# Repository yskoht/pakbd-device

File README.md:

# pakbd

## rev1

## rev2

## rev3

## License

This software is released under the MIT License, see LICENSE.

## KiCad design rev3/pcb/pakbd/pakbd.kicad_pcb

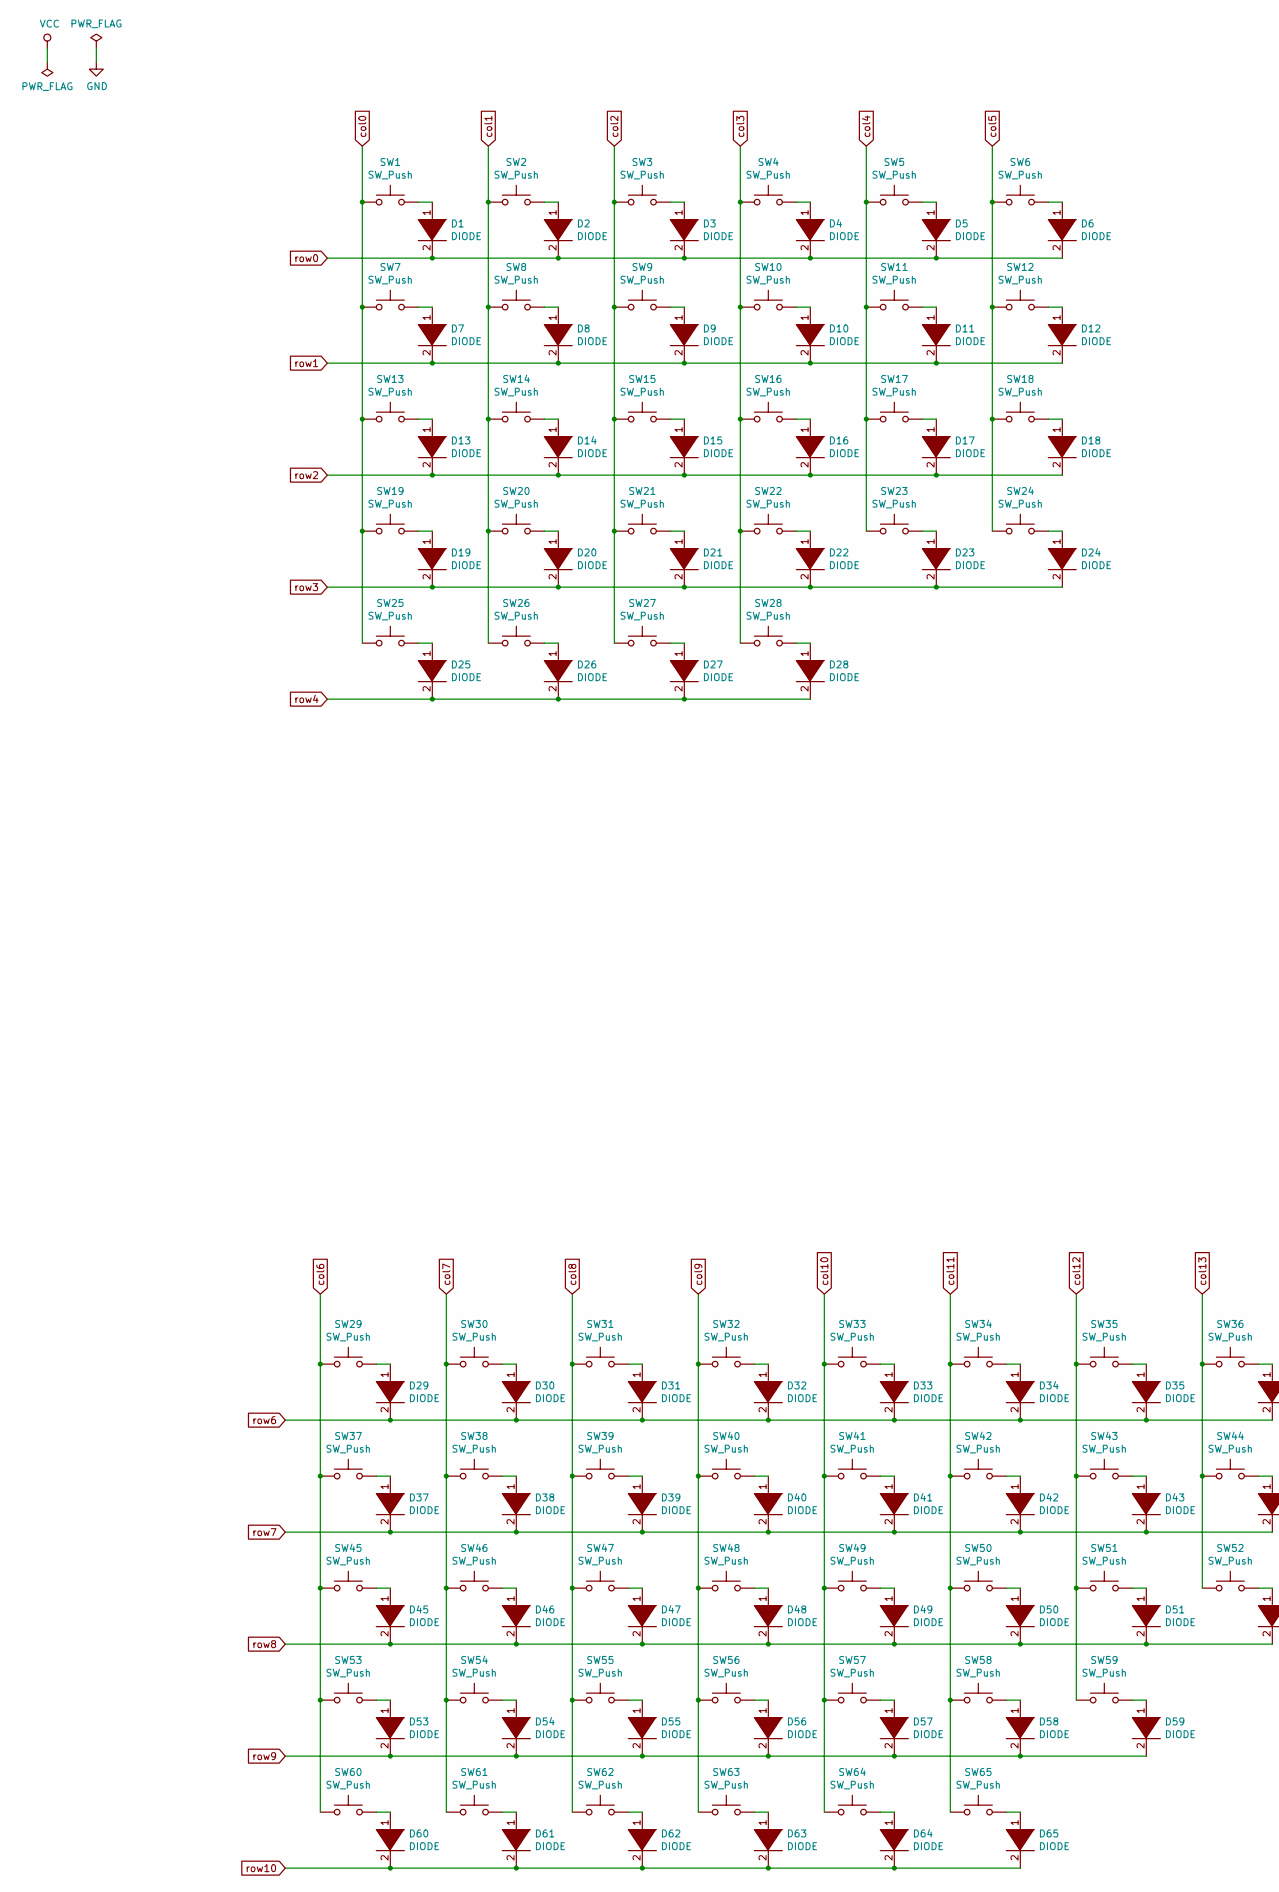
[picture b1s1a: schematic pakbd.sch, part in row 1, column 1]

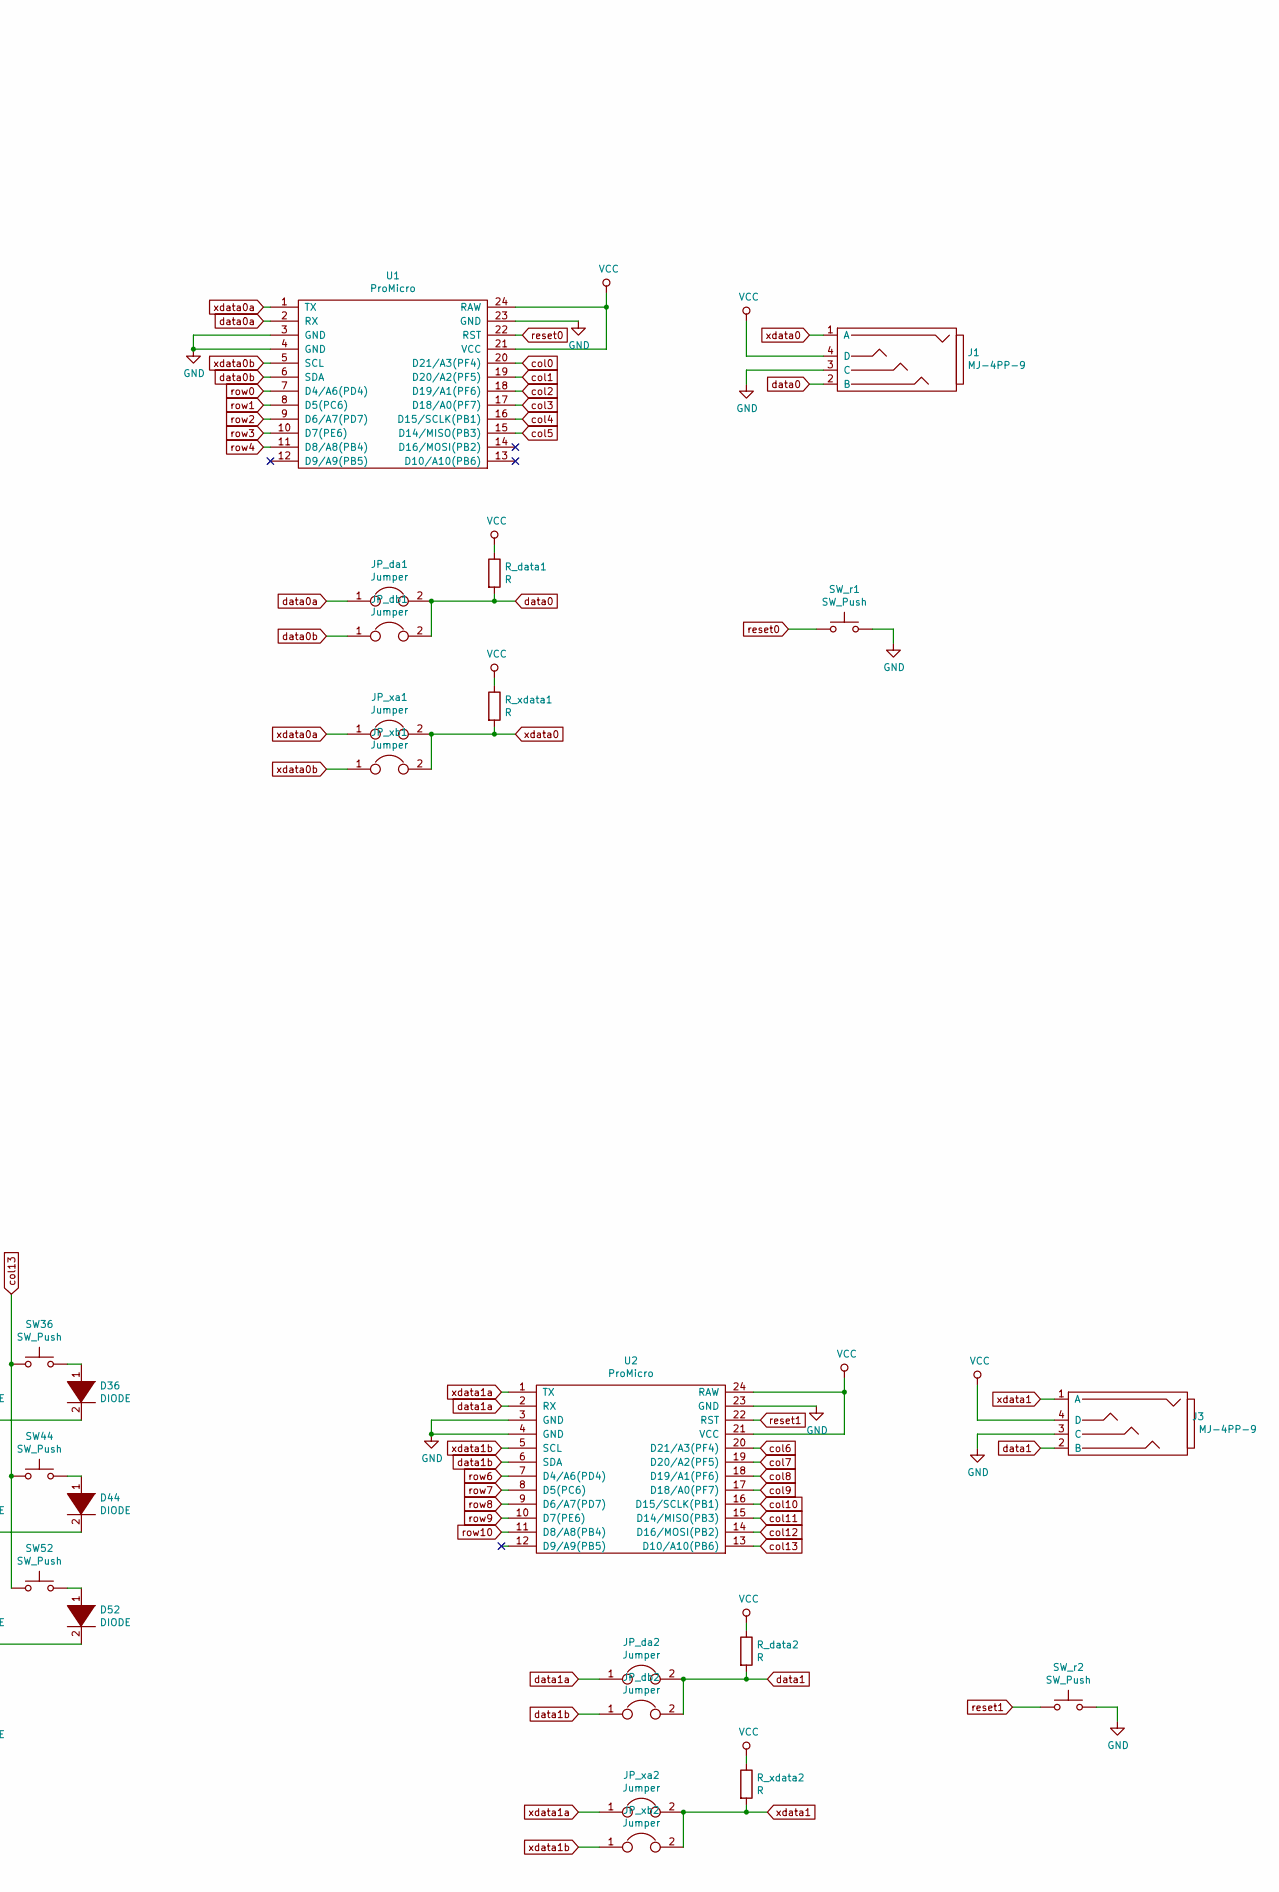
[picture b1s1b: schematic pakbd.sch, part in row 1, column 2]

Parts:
D1, D2, D3, D4, D5, D6, D7, D8, D9, D10, D11, D12, D13, D14, D15, D16, D17, D18, D19, D20, D21, D22, D23, D24, D25, D26, D27, D28, D29, D30, D31, D32, D33, D34, D35, D36, D37, D38, D39, D40, D41, D42, D43, D44, D45, D46, D47, D48, D49, D50, D51, D52, D53, D54, D55, D56, D57, D58, D59, D60, D61, D62, D63, D64, D65: DIODE; D_1206_3216Metric_Pad1.42x1.75mm_HandSolder
J1, J3: MJ-4PP-9
JP_da1, JP_da2: Jumper; SolderJumper-2_P1.3mm_Open_Pad1.0x1.5mm
JP_db1, JP_db2: Jumper; SolderJumper-2_P1.3mm_Open_Pad1.0x1.5mm
JP_xa1, JP_xa2: Jumper; SolderJumper-2_P1.3mm_Open_Pad1.0x1.5mm
JP_xb1, JP_xb2: Jumper; SolderJumper-2_P1.3mm_Open_Pad1.0x1.5mm
R_data1, R_data2: R; R_1206_3216Metric_Pad1.42x1.75mm_HandSolder
R_xdata1, R_xdata2: R; R_1206_3216Metric_Pad1.42x1.75mm_HandSolder
SW1, SW2, SW3, SW4, SW5, SW6, SW8, SW9, SW10, SW11, SW12, SW14, SW15, SW16, SW17, SW18, SW20, SW21, SW22, SW23, SW24, SW28, SW29, SW30, SW31, SW32, SW33, SW34, SW35, SW36, SW37, SW38, SW39, SW40, SW41, SW42, SW43, SW45, SW46, SW47, SW48, SW49, SW50, SW52, SW53, SW54, SW55, SW56, SW57, SW58, SW62, SW63, SW64, SW65: SW_Push; CPG151101S11_1.00u_PCB
SW7, SW27, SW44, SW60: SW_Push; CPG151101S11_1.50u_PCB
SW13: SW_Push; CPG151101S11_1.75u_PCB
SW19, SW51: SW_Push; CPG151101S11_2.25u_PCB
SW25, SW26, SW61: SW_Push; CPG151101S11_1.25u_PCB
SW59: SW_Push; CPG151101S11_2.75u_PCB
SW_r1, SW_r2: SW_Push; SW_Tactile_Straight_KSA0Axx1LFTR
U1, U2: ProMicro

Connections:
GND: J1.3 (C), J3.3 (C), SW_r1.2, SW_r2.2, U1.3 (GND), U1.4 (GND), U1.23 (GND), U2.3 (GND), U2.4 (GND), U2.23 (GND)
unnamed: D1.1 (K), SW1.2
unnamed: D2.1 (K), SW2.2
unnamed: D3.1 (K), SW3.2
unnamed: D4.1 (K), SW4.2
unnamed: D5.1 (K), SW5.2
unnamed: D6.1 (K), SW6.2
unnamed: D7.1 (K), SW7.2
unnamed: D8.1 (K), SW8.2
unnamed: D9.1 (K), SW9.2
unnamed: D10.1 (K), SW10.2
unnamed: D11.1 (K), SW11.2
unnamed: D12.1 (K), SW12.2
unnamed: D13.1 (K), SW13.2
unnamed: D14.1 (K), SW14.2
unnamed: D15.1 (K), SW15.2
unnamed: D16.1 (K), SW16.2
unnamed: D17.1 (K), SW17.2
unnamed: D18.1 (K), SW18.2
unnamed: D19.1 (K), SW19.2
unnamed: D20.1 (K), SW20.2
unnamed: D21.1 (K), SW21.2
unnamed: D22.1 (K), SW22.2
unnamed: D23.1 (K), SW23.2
unnamed: D24.1 (K), SW24.2
unnamed: D25.1 (K), SW25.2
unnamed: D26.1 (K), SW26.2
unnamed: D27.1 (K), SW27.2
unnamed: D28.1 (K), SW28.2
unnamed: D29.1 (K), SW29.2
unnamed: D30.1 (K), SW30.2
unnamed: D31.1 (K), SW31.2
unnamed: D32.1 (K), SW32.2
unnamed: D33.1 (K), SW33.2
unnamed: D34.1 (K), SW34.2
unnamed: D35.1 (K), SW35.2
unnamed: D36.1 (K), SW36.2
unnamed: D37.1 (K), SW37.2
unnamed: D38.1 (K), SW38.2
unnamed: D39.1 (K), SW39.2
unnamed: D40.1 (K), SW40.2
unnamed: D41.1 (K), SW41.2
unnamed: D42.1 (K), SW42.2
unnamed: D43.1 (K), SW43.2
unnamed: D44.1 (K), SW44.2
unnamed: D45.1 (K), SW45.2
unnamed: D46.1 (K), SW46.2
unnamed: D47.1 (K), SW47.2
unnamed: D48.1 (K), SW48.2
unnamed: D49.1 (K), SW49.2
unnamed: D50.1 (K), SW50.2
unnamed: D51.1 (K), SW51.2
unnamed: D52.1 (K), SW52.2
unnamed: D53.1 (K), SW53.2
unnamed: D54.1 (K), SW54.2
unnamed: D55.1 (K), SW55.2
unnamed: D56.1 (K), SW56.2
unnamed: D57.1 (K), SW57.2
unnamed: D58.1 (K), SW58.2
unnamed: D59.1 (K), SW59.2
unnamed: D60.1 (K), SW60.2
unnamed: D61.1 (K), SW61.2
unnamed: D62.1 (K), SW62.2
unnamed: D63.1 (K), SW63.2
unnamed: D64.1 (K), SW64.2
unnamed: D65.1 (K), SW65.2
VCC: J1.4 (D), J3.4 (D), R_data1.1, R_data2.1, R_xdata1.1, R_xdata2.1, U1.21 (VCC), U1.24 (RAW), U2.21 (VCC), U2.24 (RAW)
col0: SW1.1, SW7.1, SW13.1, SW19.1, SW25.1, U1.20 (D21/A3(PF4))
col1: SW2.1, SW8.1, SW14.1, SW20.1, SW26.1, U1.19 (D20/A2(PF5))
col2: SW3.1, SW9.1, SW15.1, SW21.1, SW27.1, U1.18 (D19/A1(PF6))
col3: SW4.1, SW10.1, SW16.1, SW22.1, SW28.1, U1.17 (D18/A0(PF7))
col4: SW5.1, SW11.1, SW17.1, SW23.1, U1.16 (D15/SCLK(PB1))
col5: SW6.1, SW12.1, SW18.1, SW24.1, U1.15 (D14/MISO(PB3))
col6: SW29.1, SW37.1, SW45.1, SW53.1, SW60.1, U2.20 (D21/A3(PF4))
col7: SW30.1, SW38.1, SW46.1, SW54.1, SW61.1, U2.19 (D20/A2(PF5))
col8: SW31.1, SW39.1, SW47.1, SW55.1, SW62.1, U2.18 (D19/A1(PF6))
col9: SW32.1, SW40.1, SW48.1, SW56.1, SW63.1, U2.17 (D18/A0(PF7))
col10: SW33.1, SW41.1, SW49.1, SW57.1, SW64.1, U2.16 (D15/SCLK(PB1))
col11: SW34.1, SW42.1, SW50.1, SW58.1, SW65.1, U2.15 (D14/MISO(PB3))
col12: SW35.1, SW43.1, SW51.1, SW59.1, U2.14 (D16/MOSI(PB2))
col13: SW36.1, SW44.1, SW52.1, U2.13 (D10/A10(PB6))
data0: J1.2 (B), JP_da1.2, JP_db1.2, R_data1.2
data0a: JP_da1.1, U1.2 (RX)
data0b: JP_db1.1, U1.6 (SDA)
data1: J3.2 (B), JP_da2.2, JP_db2.2, R_data2.2
data1a: JP_da2.1, U2.2 (RX)
data1b: JP_db2.1, U2.6 (SDA)
reset0: SW_r1.1, U1.22 (RST)
reset1: SW_r2.1, U2.22 (RST)
row0: D1.2 (A), D2.2 (A), D3.2 (A), D4.2 (A), D5.2 (A), D6.2 (A), U1.7 (D4/A6(PD4))
row1: D7.2 (A), D8.2 (A), D9.2 (A), D10.2 (A), D11.2 (A), D12.2 (A), U1.8 (D5(PC6))
row2: D13.2 (A), D14.2 (A), D15.2 (A), D16.2 (A), D17.2 (A), D18.2 (A), U1.9 (D6/A7(PD7))
row3: D19.2 (A), D20.2 (A), D21.2 (A), D22.2 (A), D23.2 (A), D24.2 (A), U1.10 (D7(PE6))
row4: D25.2 (A), D26.2 (A), D27.2 (A), D28.2 (A), U1.11 (D8/A8(PB4))
row6: D29.2 (A), D30.2 (A), D31.2 (A), D32.2 (A), D33.2 (A), D34.2 (A), D35.2 (A), D36.2 (A), U2.7 (D4/A6(PD4))
row7: D37.2 (A), D38.2 (A), D39.2 (A), D40.2 (A), D41.2 (A), D42.2 (A), D43.2 (A), D44.2 (A), U2.8 (D5(PC6))
row8: D45.2 (A), D46.2 (A), D47.2 (A), D48.2 (A), D49.2 (A), D50.2 (A), D51.2 (A), D52.2 (A), U2.9 (D6/A7(PD7))
row9: D53.2 (A), D54.2 (A), D55.2 (A), D56.2 (A), D57.2 (A), D58.2 (A), D59.2 (A), U2.10 (D7(PE6))
row10: D60.2 (A), D61.2 (A), D62.2 (A), D63.2 (A), D64.2 (A), D65.2 (A), U2.11 (D8/A8(PB4))
xdata0: J1.1 (A), JP_xa1.2, JP_xb1.2, R_xdata1.2
xdata0a: JP_xa1.1, U1.1 (TX)
xdata0b: JP_xb1.1, U1.5 (SCL)
xdata1: J3.1 (A), JP_xa2.2, JP_xb2.2, R_xdata2.2
xdata1a: JP_xa2.1, U2.1 (TX)
xdata1b: JP_xb2.1, U2.5 (SCL)

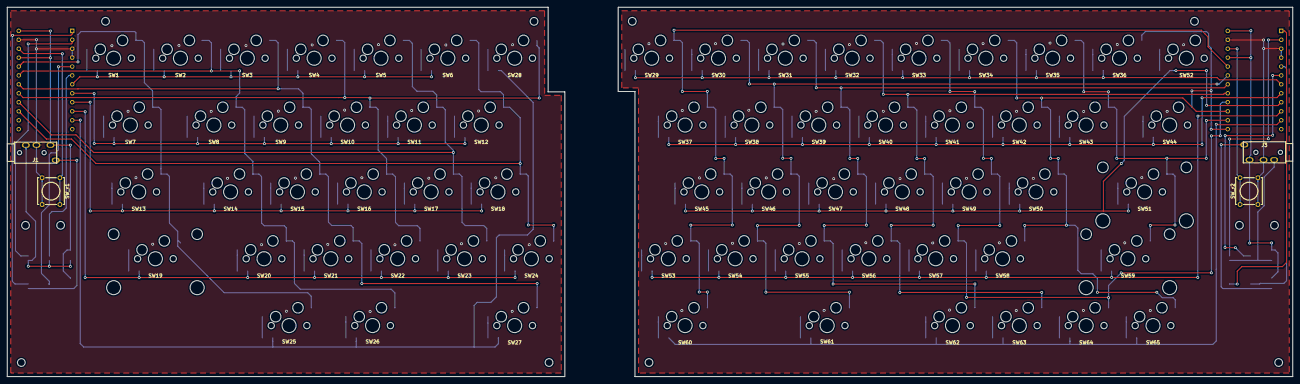
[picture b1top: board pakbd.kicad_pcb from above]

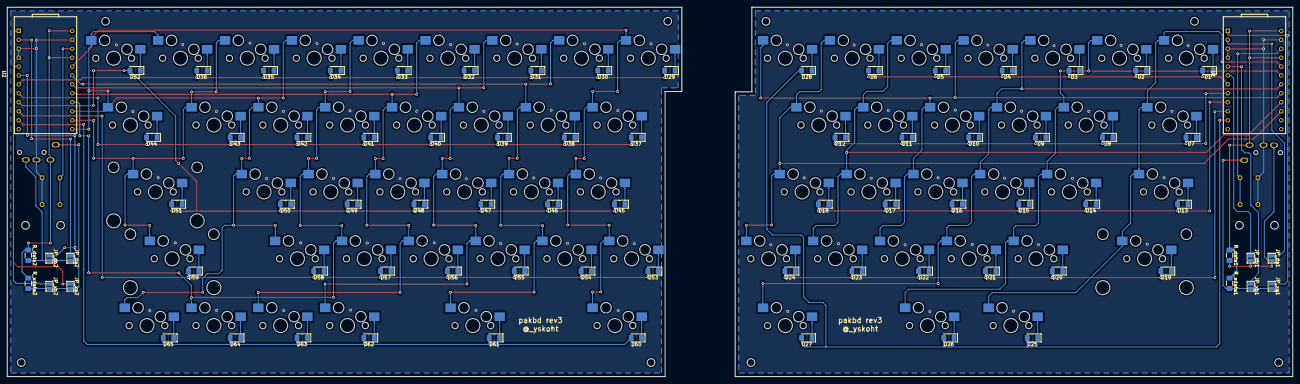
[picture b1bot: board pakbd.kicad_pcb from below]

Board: 2 copper layers, 366.4 x 105.2 mm, 148 parts (79 on the bottom side), 105 nets.

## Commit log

2018-10-07 Add submodule
2018-10-07 Add .gitignore
2018-10-07 Add schema
2018-10-09 Add footprint
2018-10-12 Add wiring
2018-10-13 Add gerber
2018-10-13 Add dwgs.user
2018-10-13 Add case
2018-10-18 Mod case
2019-02-17 Add rev2 pcb
2019-02-17 Add rev2 case
2019-03-02 Add rev3 pcb
2019-03-03 Add rev3 case
2019-03-03 Convert gerber to zip
2019-03-08 fix rev3 case
2019-03-13 add tmp
2019-03-16 add rev3 case .ai
2019-09-28 Create LICENSE
2019-09-28 Add images
2019-09-28 Add README.md
